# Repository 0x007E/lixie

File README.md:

# LED Nixie Clock

Kurzbeschreibung

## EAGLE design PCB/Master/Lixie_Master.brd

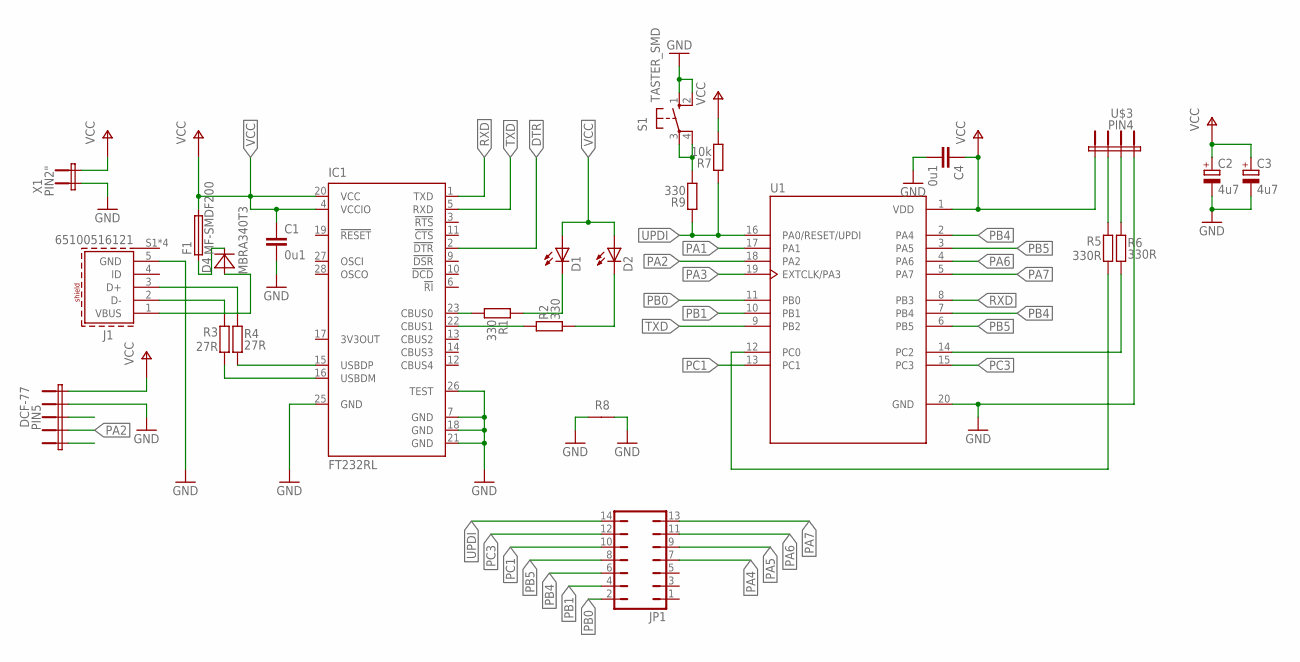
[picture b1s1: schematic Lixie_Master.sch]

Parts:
C1, C4: 0u1; C0805
C2, C3: 4u7; 153CLV-0405
D1, D2: LED1206; 1206
D4: MBRA340T3; SMA
DCF-77: PIN5
F1: MF-SMDF200; MF-SMDF050
IC1: FT232RL; SSOP28
J1: 65100516121
JP1: JP7Q
R1, R2, R9: 330; R0805
R3, R4: 27R; R1206
R5, R6: 330R; R1206
R7: 10k; R0805
R8: R0/10
S1: TASTER_SMD
U1: ATTINY-406SN; SOIC127P1032X265-20N
U$3: PIN4; PIN4_P
X1: PIN2"; PIN2

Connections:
DTR: IC1.2 (!DTR)
GND: C1.2, C2.-, C3.-, C4.2, DCF-77.4, IC1.7 (GND), IC1.18 (GND), IC1.21 (GND), IC1.25 (GND), IC1.26 (TEST), J1.5 (GND), R8.1, R8.2, S1.1 (S), S1.2 (S1), U1.20 (GND), U$3.4, X1.P$2 (KL1)
unnamed: J1.3 (D+), R4.2
unnamed: IC1.16 (USBDM), R3.1
unnamed: IC1.23 (CBUS0), R1.1
unnamed: J1.2 (D-), R3.2
unnamed: D1.C, R1.2
unnamed: IC1.22 (CBUS1), R2.2
unnamed: D2.C, R2.1
unnamed: R5.1, U1.12 (PC0)
unnamed: R6.1, U1.14 (PC2)
unnamed: IC1.15 (USBDP), R4.1
unnamed: D4.C, F1.1
unnamed: R5.2, U$3.2
unnamed: R6.2, U$3.3
unnamed: D4.A, J1.1 (VBUS)
unnamed: R9.1, S1.3, S1.4 (P1)
PA1: U1.17 (PA1)
PA2: DCF-77.2, U1.18 (PA2)
PA3: U1.19 (EXTCLK/PA3)
PA4: JP1.7
PA5: JP1.9
PA6: JP1.11, U1.4 (PA6)
PA7: JP1.13, U1.5 (PA7)
PB0: JP1.2, U1.11 (PB0)
PB1: JP1.4, U1.10 (PB1)
PB4: JP1.6, U1.2 (PA4), U1.7 (PB4)
PB5: JP1.8, U1.3 (PA5), U1.6 (PB5)
PC1: JP1.10, U1.13 (PC1)
PC3: JP1.12, U1.15 (PC3)
RXD: IC1.1 (TXD), U1.8 (PB3)
TXD: IC1.5 (RXD), U1.9 (PB2)
UPDI: JP1.14, R7.2, R9.2, U1.16 (PA0/RESET/UPDI)
VCC: C1.1, C2.+, C3.+, C4.1, D1.A, D2.A, DCF-77.5, F1.2, IC1.4 (VCCIO), IC1.20 (VCC), R7.1, U1.1 (VDD), U$3.1, X1.P$3 (KL2)

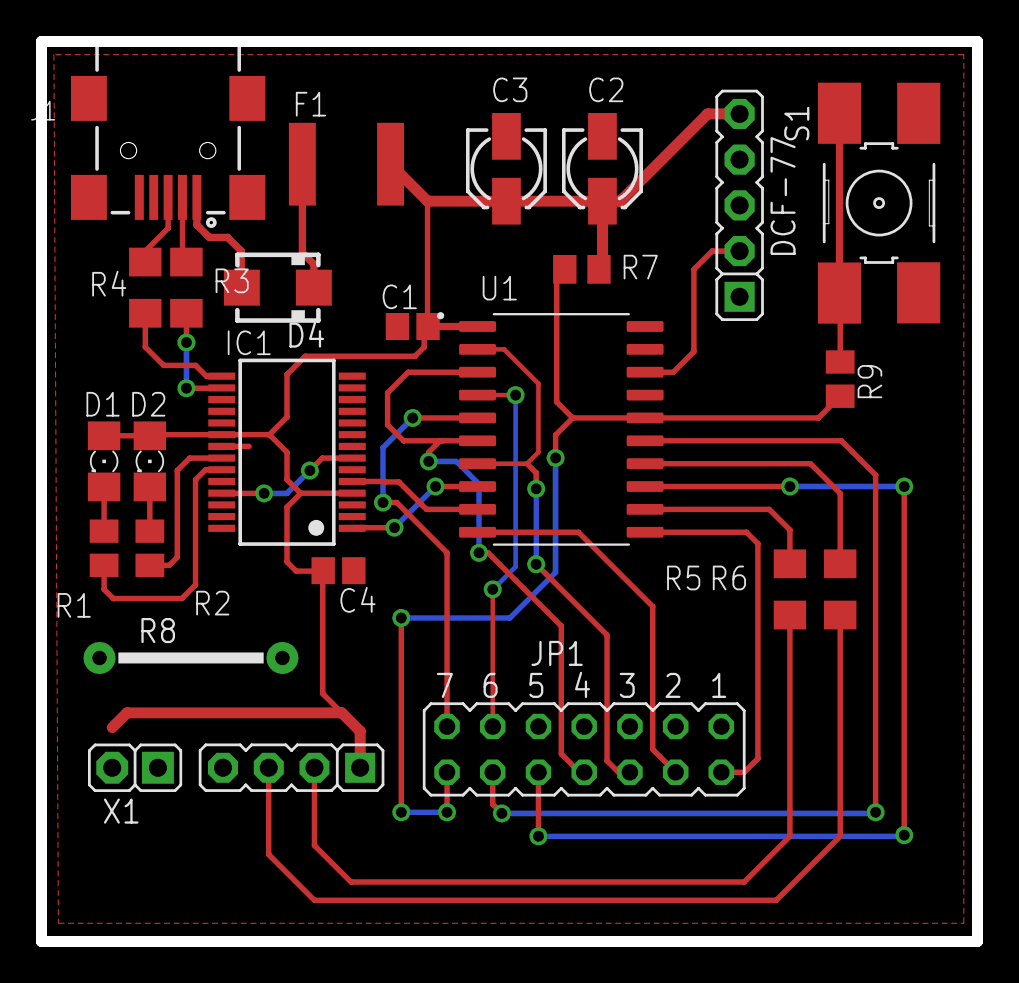
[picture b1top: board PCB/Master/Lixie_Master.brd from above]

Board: 2 copper layers, 52.0 x 50.0 mm, 25 parts (0 on the bottom side), 29 nets.

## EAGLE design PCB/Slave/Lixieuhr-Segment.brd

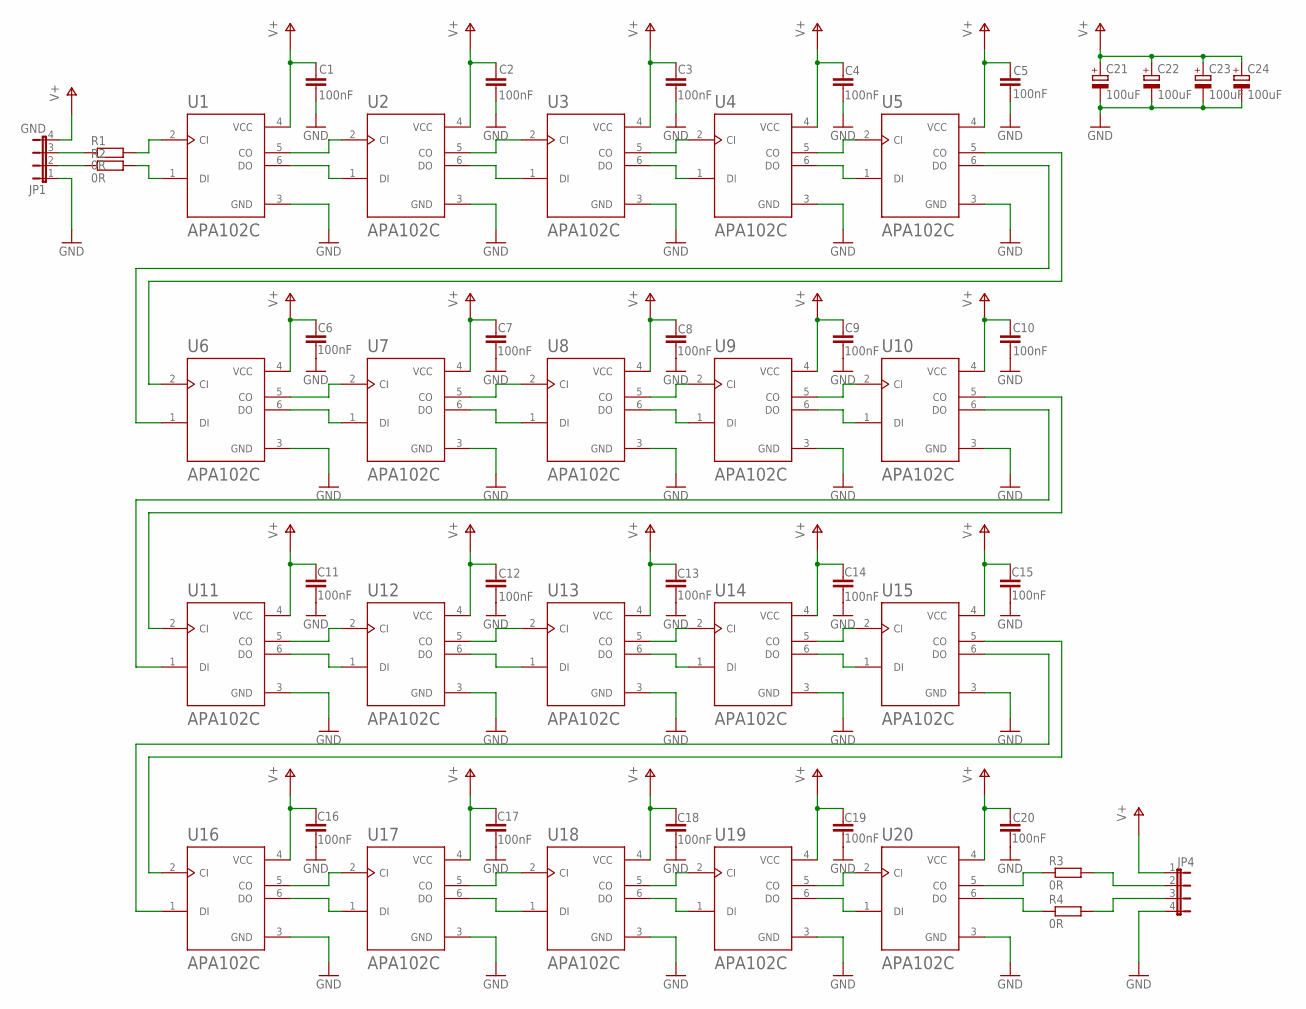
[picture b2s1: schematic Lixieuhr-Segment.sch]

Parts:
C1, C2, C3, C4, C5, C6, C7, C8, C9, C10, C11, C12, C13, C14, C15, C16, C17, C18, C19, C20: 100nF; C0805
C21, C22, C23, C24: 100uF; 153CLV-0405
JP1: GND; JP4
JP4: JP4E; JP4
R1, R2, R3, R4: 0R; R1206
U1, U2, U3, U4, U5, U6, U7, U8, U9, U10, U11, U12, U13, U14, U15, U16, U17, U18, U19, U20: APA102C; SON160P500X500X140-6N

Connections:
GND: C1.1, C2.1, C3.1, C4.1, C5.1, C6.1, C7.1, C8.1, C9.1, C10.1, C11.1, C12.1, C13.1, C14.1, C15.1, C16.1, C17.1, C18.1, C19.1, C20.1, C21.-, C22.-, C23.-, C24.-, JP1.1, JP4.4, U1.3 (GND), U2.3 (GND), U3.3 (GND), U4.3 (GND), U5.3 (GND), U6.3 (GND), U7.3 (GND), U8.3 (GND), U9.3 (GND), U10.3 (GND), U11.3 (GND), U12.3 (GND), U13.3 (GND), U14.3 (GND), U15.3 (GND), U16.3 (GND), U17.3 (GND), U18.3 (GND), U19.3 (GND), U20.3 (GND)
unnamed: U1.5 (CO), U2.2 (CI)
unnamed: U2.5 (CO), U3.2 (CI)
unnamed: U3.5 (CO), U4.2 (CI)
unnamed: U4.5 (CO), U5.2 (CI)
unnamed: R2.2, U1.1 (DI)
unnamed: U6.5 (CO), U7.2 (CI)
unnamed: U7.5 (CO), U8.2 (CI)
unnamed: U8.5 (CO), U9.2 (CI)
unnamed: U9.5 (CO), U10.2 (CI)
unnamed: U1.6 (DO), U2.1 (DI)
unnamed: U2.6 (DO), U3.1 (DI)
unnamed: U3.6 (DO), U4.1 (DI)
unnamed: U4.6 (DO), U5.1 (DI)
unnamed: JP1.2, R2.1
unnamed: U9.6 (DO), U10.1 (DI)
unnamed: U6.6 (DO), U7.1 (DI)
unnamed: U7.6 (DO), U8.1 (DI)
unnamed: U8.6 (DO), U9.1 (DI)
unnamed: U5.5 (CO), U6.2 (CI)
unnamed: R1.2, U1.2 (CI)
unnamed: U10.5 (CO), U11.2 (CI)
unnamed: U10.6 (DO), U11.1 (DI)
unnamed: U11.5 (CO), U12.2 (CI)
unnamed: U12.5 (CO), U13.2 (CI)
unnamed: U13.5 (CO), U14.2 (CI)
unnamed: U14.5 (CO), U15.2 (CI)
unnamed: U16.5 (CO), U17.2 (CI)
unnamed: U17.5 (CO), U18.2 (CI)
unnamed: U18.5 (CO), U19.2 (CI)
unnamed: U19.5 (CO), U20.2 (CI)
unnamed: U11.6 (DO), U12.1 (DI)
unnamed: U12.6 (DO), U13.1 (DI)
unnamed: U13.6 (DO), U14.1 (DI)
unnamed: U14.6 (DO), U15.1 (DI)
unnamed: JP1.3, R1.1
unnamed: U19.6 (DO), U20.1 (DI)
unnamed: U16.6 (DO), U17.1 (DI)
unnamed: U17.6 (DO), U18.1 (DI)
unnamed: U18.6 (DO), U19.1 (DI)
unnamed: R3.1, U20.5 (CO)
unnamed: JP4.2, R3.2
unnamed: JP4.3, R4.2
unnamed: R4.1, U20.6 (DO)
unnamed: U5.6 (DO), U6.1 (DI)
unnamed: U15.5 (CO), U16.2 (CI)
unnamed: U15.6 (DO), U16.1 (DI)
V+: C1.2, C2.2, C3.2, C4.2, C5.2, C6.2, C7.2, C8.2, C9.2, C10.2, C11.2, C12.2, C13.2, C14.2, C15.2, C16.2, C17.2, C18.2, C19.2, C20.2, C21.+, C22.+, C23.+, C24.+, JP1.4, JP4.1, U1.4 (VCC), U2.4 (VCC), U3.4 (VCC), U4.4 (VCC), U5.4 (VCC), U6.4 (VCC), U7.4 (VCC), U8.4 (VCC), U9.4 (VCC), U10.4 (VCC), U11.4 (VCC), U12.4 (VCC), U13.4 (VCC), U14.4 (VCC), U15.4 (VCC), U16.4 (VCC), U17.4 (VCC), U18.4 (VCC), U19.4 (VCC), U20.4 (VCC)

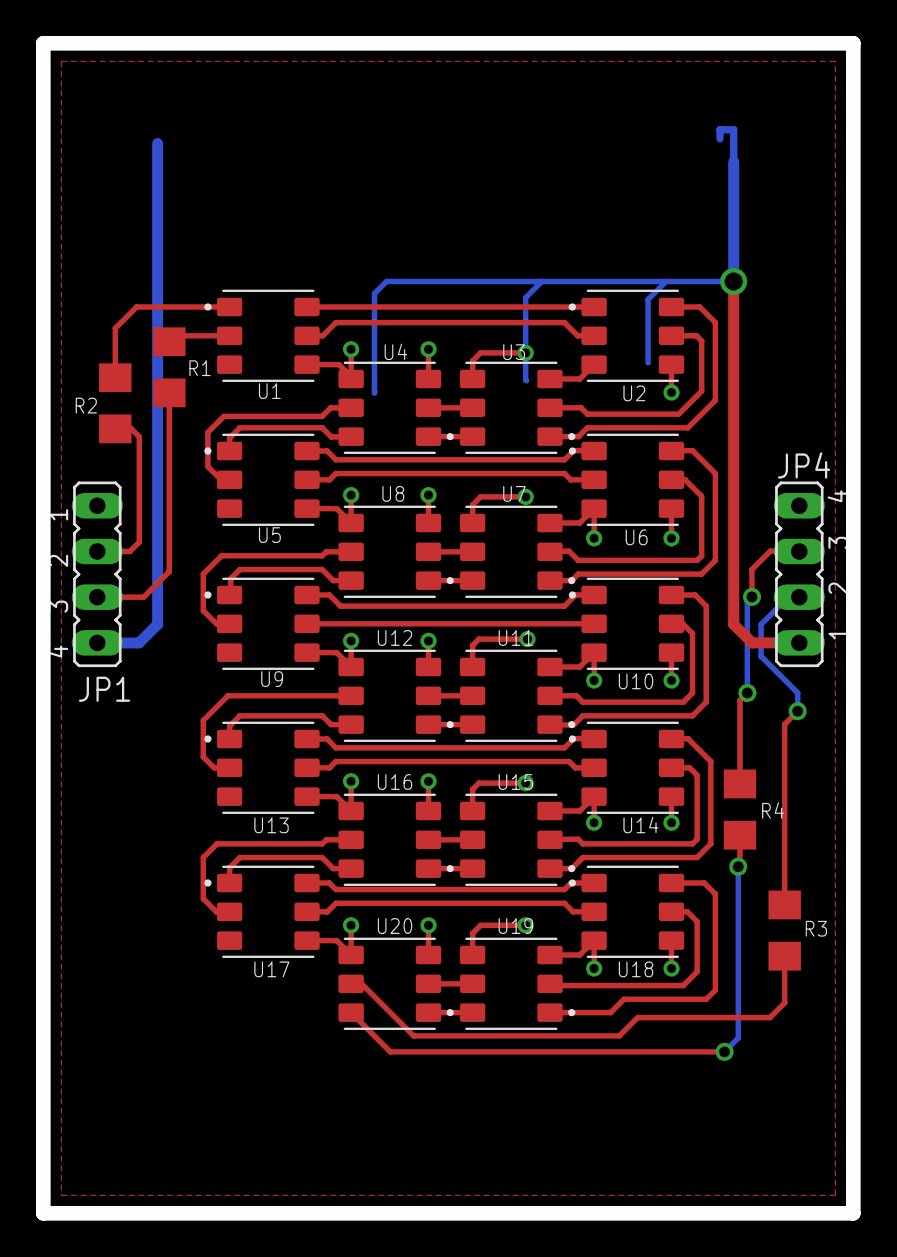
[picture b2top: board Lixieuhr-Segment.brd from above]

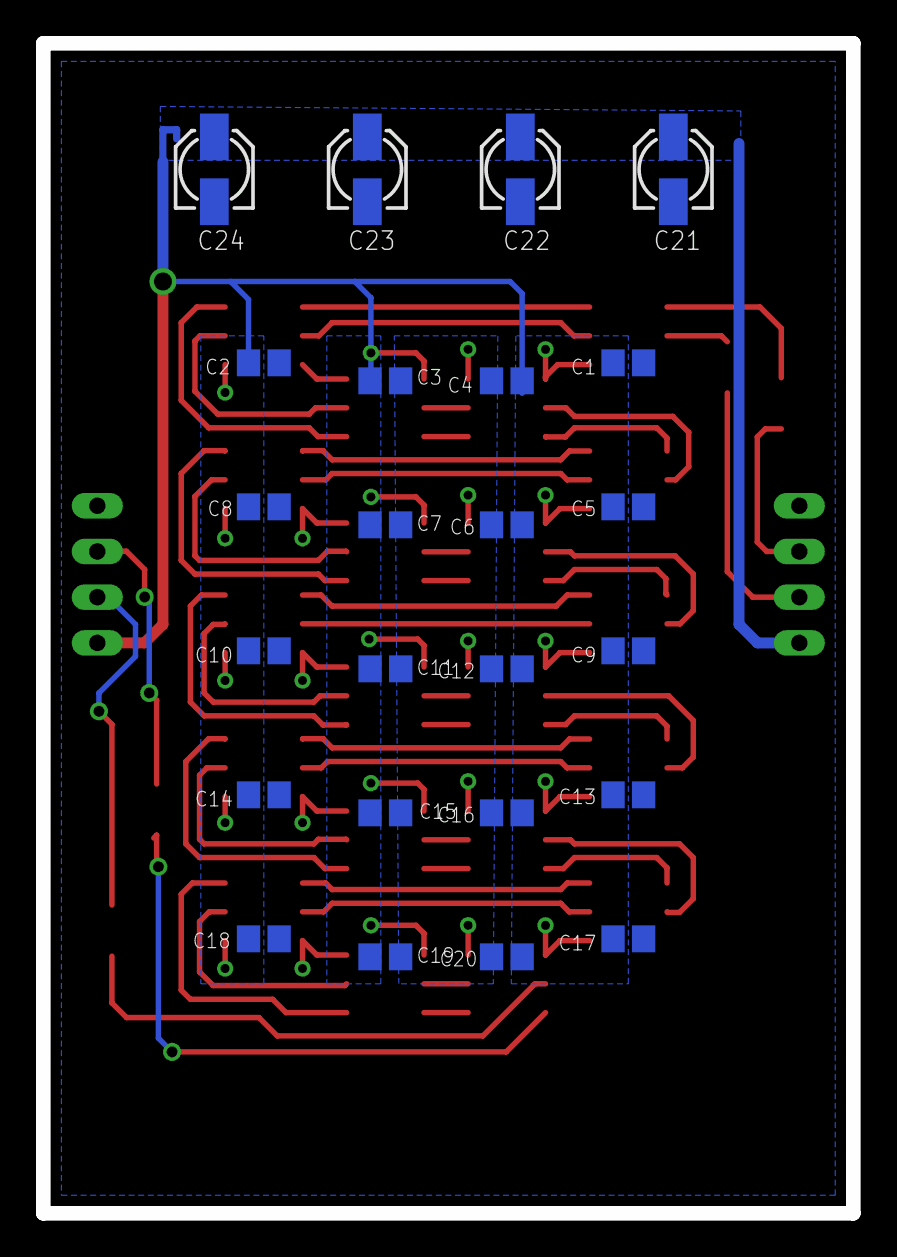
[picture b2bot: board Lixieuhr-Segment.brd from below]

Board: 2 copper layers, 45.0 x 65.0 mm, 50 parts (24 on the bottom side), 48 nets.

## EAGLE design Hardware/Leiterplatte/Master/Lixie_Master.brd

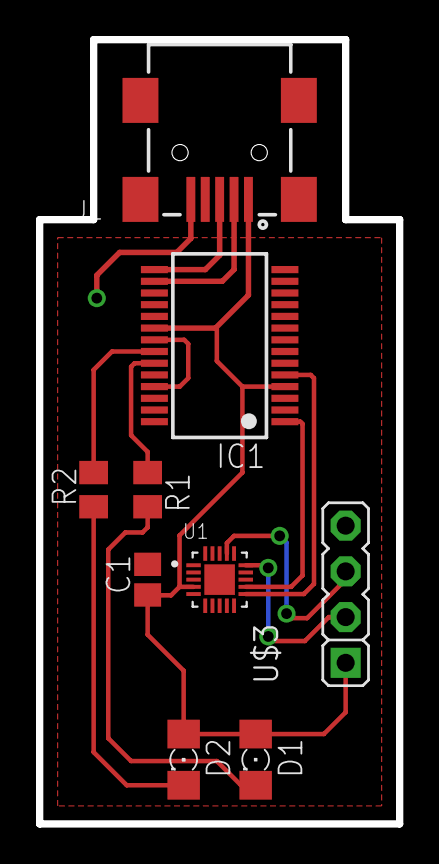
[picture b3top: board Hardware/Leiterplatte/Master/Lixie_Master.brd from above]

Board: 2 copper layers, 20.0 x 43.6 mm, 9 parts (0 on the bottom side), 12 nets.

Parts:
C1: 0u1; C0805
D1, D2: 1206
IC1: FT232RL; SSOP28
J1: 65100516121
R1, R2: R0805
U1: ATTINY406-MFR; QFN40P300X300X90-21N
U$3: PIN4; PIN4_P

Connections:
GND: C1.2, IC1.7, IC1.18, IC1.21, IC1.25, IC1.26, J1.5, U1.3, U$3.4
unnamed: IC1.15, J1.3
unnamed: IC1.16, J1.2
unnamed: IC1.23, R1.1
unnamed: D1.C, R1.2
unnamed: IC1.22, R2.2
unnamed: D2.C, R2.1
unnamed: U1.15, U$3.2
unnamed: U1.17, U$3.3
RXD: IC1.5, U1.11
TXD: IC1.1, U1.12
VCC: C1.1, D1.A, D2.A, IC1.4, IC1.20, J1.1, U1.4, U$3.1

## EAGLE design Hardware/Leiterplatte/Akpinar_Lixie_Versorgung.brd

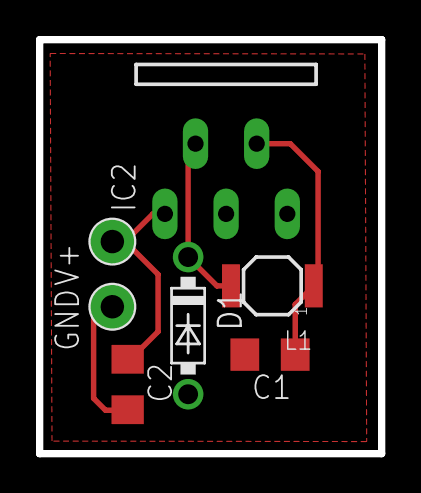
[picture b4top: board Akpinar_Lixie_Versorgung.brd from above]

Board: 2 copper layers, 19.0 x 23.0 mm, 8 parts (0 on the bottom side), 4 nets.

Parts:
C1: 330uF; C1206
C2: 100uF; C1206
D1: 1N5819-B; DO41-7.6
FRAME1: HTL-A4-HA4H; HTL-A4-H
GND: LPIN
IC2: LM2575-5.0T; TO220-5
L1: MS42
V+: LPIN

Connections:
GND: C1.2, C2.2, D1.A, GND.P$1, IC2.3, IC2.5
unnamed: D1.C, IC2.2, L1.1
unnamed: C1.1, IC2.4, L1.2
V+: C2.1, IC2.1, V+.P$1

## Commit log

2022-11-11 Create project structure
2022-11-23 Lixie-Layout
2022-11-23 Case
2022-11-23 Datassheets/Libs
2022-12-02 Schaltpläne V02
2022-12-04 Segmentplatine_V02
2022-12-04 Segmentplatine_V03
2022-12-04 Gerber Files
2022-12-04 Lixie_Maser_V02
2022-12-09 Added APA102C Library
2022-12-09 Firmware update
2022-12-10 Some Tests
2022-12-12 Leiterplatten V05
2022-12-13 Create Herr Janz hat Drip
2022-12-13 LED Values
2022-12-14 KiCad Files
2022-12-14 Added Clock Lib
2022-12-14 Firmware Update
    Added new Solution
    Deleted folder Libraries
2022-12-14 Added Structogram
2022-12-14 Added Time Settings via UART
2022-12-14 Minor Changes
2022-12-14 Added ATtiny406 Project
2022-12-22 Master
2022-12-22 Lixie Bestellliste Update
2022-12-23 Bestelllisten
2022-12-24 Update Bestellung
2023-01-08 Gehäuse_aktuell
2023-01-10 Layout
2023-01-31 Lixie Update
2023-02-01 Lixie Attiny1606 Anpassung
    Der Atmega16 Code wurde an den Attiny1606 angepasst.
2023-02-01 SPI Update
2023-02-01 Struktogramm Update
    ISR und Datenstransfer Struktogramm Update
2023-02-05 Optimierung
2023-02-05 Usb Anschluss
2023-02-08 Struktogramme Hinzugefügt
2023-02-08 Dokumentation Update
2023-02-08 Optimieren
2023-02-22 Kommentare Hinzugefügt (09:10)
2023-02-23 Optimierung von Gehäuse und 3D printerstellung
2023-03-01 Firmware Atmega16 Update (Clock Fix)
    Bug Fixes
2023-03-01 Messprotokoll Bilder
    Strommessung
2023-03-03 Platinentest Update
2023-03-03 Firmware Update
    Attiny Firmware Update
    -SPI
    -Clock
2023-03-09 080323
2023-03-15 Firmware Update
    -Auf der Platine wurden TxD und RxD vertauscht
    -Neue Platinen wurden Bestellt
2023-03-16 Doku Update
2023-03-17 Funktion
2023-03-18 Lixie Firmware Update / Doku Update
2023-03-18 Software Dokumentation Update
2023-03-18 Quellen Hinzugefügt
2023-03-18 Update Doku Update
2023-03-18 Update Doku Software
2023-03-19 Update Dokumentation (Zeitplan)
2023-03-22 Lixie Firmware Update
    -Kann ohne UPDI gestartet werden
2023-03-24 USART Menu Update
2023-03-29 USART Update
    USART Interface finished
2023-03-29 Kleine Programmänderung
2023-04-04 Deleted unrelated files
2023-04-12 Abgeschlossene Dokumentation Hinzugefügt

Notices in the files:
parts and their libraries:
SOIC127P1032X265-20N: © 2018 Microchip Technology Inc. Datasheet Preliminary DS40001976A-page 1
